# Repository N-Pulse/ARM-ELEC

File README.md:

# N-Pulse Prosthetic Safety System

> **EPFL N-Pulse — Spring Semester 2026**  
> Firmware and GUI for the safety monitoring board of the N-Pulse transradial bionic arm prosthesis.  
> For background on sensor selection rationale, thresholds, and design decisions, refer to the accompanying report.

---

## Repository Structure

```
/
├── GUI/
│   └── serial_dashboard.py        # Plotly Dash web dashboard — reads serial CSV and plots live telemetry
│
└── prosthetic_safety/
    ├── prosthetic_safety.ino      # Arduino sketch entry point (setup + loop)
    ├── Config.h                   # ⬅ All pin assignments, I2C addresses, thresholds — edit here first
    ├── DataTypes.h / .cpp         # Structs (TH_Reading, PowerReading, IMUReading, SafetyFlags) and global sensor objects
    ├── Setup.h / .cpp             # Sensor initialisation and interrupt attachment
    ├── Sensors.h / .cpp           # Sensor read functions (non-blocking DS18B20, SHT41, Si7021, INA260, LIS3DH)
    ├── Safety.h / .cpp            # Fault evaluation logic + ISR handlers
    ├── Logging.h / .cpp           # CSV serial output and SD card stub
    └── Utils.h / .cpp             # Helpers: ROM printing, threshold lookups, raw IMU register I/O
```

---

## Hardware Connections

The system uses two I2C buses on the Adafruit Metro ESP32-S3. Bus 0 (`Wire`, default pins) and Bus 1 (`Wire1`, pins 9 SDA / 10 SCL) are both active simultaneously.

### Pin Map (from `Config.h`)

| Signal | ESP32-S3 Pin | Connected to |
|--------|-------------|--------------|
| SDA0 | Pin SDA | DS2484 bus0, INA260, LIS3DH, SHT41 bus0 |
| SCL0 | Pin SCL | Same as above |
| SDA1 | Pin 9 | DS2484 bus1, SHT41 bus1, Si7021 |
| SCL1 | Pin 10 | Same as above |
| 1-Wire direct | Pin 7 | Battery, socket, and 1 motor DS18B20 (no bridge chip) |
| IMU interrupt | Pin 5 | LIS3DH INT1 → MCU (active-low, pull-up enabled) |
| Current alert | Pin 6 | INA260 ALERT → MCU (active-low, pull-up enabled, latching) |
| Power cut | Pin 11 | Pololu switch CTRL — pull **LOW** to cut load power |

### Wiring Diagram

#### JST cable labels

#### Current interupt test-bench wiring

Depending on the setup, it may be beneficial to make sure VIN- is the same as the systems GND (e.g. when using a lab alim), then wire like on the image (with the jumper). When trying to use the sensor on the test bench with the battery for example, simple pass the high or low cable of the battery through the VIN+ to VIN-. You might want remove the jumper and potentiometer to avoid any confusion in the wiring (unless the grounding is still useful). 

#### Full test-bench

Refer to this image to wire the test bench correctly.

Also note there are 3D printed motor mounts (orange), which can be used to test the motor under load and the thermal sensors. 

#### System-level block diagram and hand-level schematic: 

### I2C Address Map

| Device | Bus | Address | Notes |
|--------|-----|---------|-------|
| DS2484 (×2) | 0 and 1 | `0x18` | Fixed — one per bus to avoid collision |
| LIS3DH | 0 | `0x19` | SDO tied HIGH |
| INA260 | 0 | `0x40` | A0/A1 default |
| SHT41 (×2) | 0 and 1 | `0x44` | Fixed — one per bus to avoid collision |
| Si7021 | 1 | `0x40` | Shares bus 1 with SHT41, different from INA260 on bus 0 |

### DS18B20 Temperature Sensor Topology

Nine DS18B20s are distributed across three 1-Wire lines:

- **Bus 0 (via DS2484 on I2C bus 0):** 3 motor sensors in the hand
- **Bus 1 (via DS2484 on I2C bus 1):** 3 motor sensors in the hand
- **Direct line (pin 7, no bridge):** battery sensor, socket/stump contact sensor, 1 motor sensor

Each DS18B20 line needs a **4.7 kΩ pull-up resistor between DQ and 3.3 V** (but the ones passed in I2C already have a sufficient pullup resistance through the DS2484). The direct line uses the `DallasTemperature` library at **9-bit resolution** (94 ms conversion time, 0.5 °C) for faster updates. The DS2484-bridged lines use the `Adafruit_DS248x` library and the same 94 ms window.

### Power Cut Circuit

```
Battery (+) ──► Power Switch VIN ──► Prosthetic rail (+)
Battery (−) ──► Power Switch GND            ──► Prosthetic rail (−)
                        │
               ESP32-S3 Pin 11 ──► CTRL (LOW = power cut)
```

`PIN_POWER_CUT` is driven LOW by either the main loop (`requestPowerCut()`) or directly from the ISR for minimum latency on overcurrent and shock events.

---

## Sensor Discovery & Address Registration

**When new DS18B20 sensors are installed, their ROM addresses must be registered in `Config.h`.** (This should be already correct if the test-bench wasn't changed.) The firmware will print every discovered ROM to the serial monitor at startup — run the sketch once, note the ROM codes, then fill in the `bus0_sensors[]`, `bus1_sensors[]`, and `direct_sensors[]` arrays with the appropriate `SensorPurpose` and per-sensor temperature limit.

```cpp
// Example entry in Config.h
static constexpr SensorMapping direct_sensors[] = {
  {{ 0x28, 0xFF, 0x64, 0x0E, 0x6D, 0x54, 0x36, 0xC9 }, SensorPurpose::BATTERY, 45.0f },
  {{ 0x28, 0xFF, 0x64, 0x0E, 0x6D, 0x86, 0x2C, 0xE3 }, SensorPurpose::SOCKET,  41.0f },
  ...
};
```

Per-sensor limits (battery: 45 °C, socket contact: 41 °C, motors: 85 °C) are looked up at runtime by ROM address in `getSensorTempLimit()` (`Utils.cpp`). If a sensor's ROM is not in the table, it falls back to `MAX_TEMP_C`.

---

## INA260 Current Sensor — Bench Test

The INA260 sits in **series** with the battery. Before installing in the arm, validate it on a bench:

### Wiring for the test

```
Bench PSU (+) ──► INA260 IN+ ──► INA260 IN− ──► Load ──► Bench PSU (−)
                     │
              I2C to ESP32-S3 (bus 0, address 0x40)
              ALERT pin → ESP32-S3 pin 6
```

> ⚠️ The INA260 has **no galvanic isolation** between the battery ground and the board ground. Make sure both share the same ground reference, or use an isolated bench PSU. (That is the case on the test-bench)

### Recommended bench settings

| Parameter | Value |
|-----------|-------|
| PSU voltage | **12 V** |
| PSU current limit | **100 mA** |

The alert pin is configured in hardware for **overcurrent** (fires when current exceeds `Config::MAX_CURRENT_MA`). During bench testing, `MAX_CURRENT_MA` is set to 40 mA so the alert fires well within the PSU limit — set it back to 5300 mA (or appropriate value) for normal prosthetic operation.

---

## Arduino Libraries Required

Install all of the following via the Arduino Library Manager before compiling:

| Library | Used for |
|---------|---------|
| `Adafruit_INA260` | Current/voltage sensor |
| `Adafruit_LIS3DH` + `Adafruit_Sensor` | IMU |
| `Adafruit_Si7021` | Humidity/temp sensor (socket) |
| `7semi_SHT4x` | Humidity/temp sensors (hand/wrist) |
| `Adafruit_DS248x` | I2C-to-1-Wire bridge (DS2484) |
| `DallasTemperature` | Direct 1-Wire DS18B20 (no bridge) |
| `OneWire` | Required by DallasTemperature |

**Board:** Adafruit Metro ESP32-S3 (install via Arduino Boards Manager → search "esp32" by Espressif).

---

## Uploading the Firmware

1. Open `prosthetic_safety/prosthetic_safety.ino` in Arduino IDE.
2. Select **Board → Adafruit Metro ESP32-S3** and the correct COM/tty port.
3. Upload. On first boot, watch the serial monitor at **115 200 baud** — setup messages are prefixed with `[SETUP]`. Any sensor not found will print a warning; the ROM addresses of all discovered DS18B20s are printed here for registration.

---

## GUI — Live Telemetry Dashboard

`GUI/serial_dashboard.py` is a Plotly Dash web app. It reads the CSV stream from the serial port and displays five real-time subplots plus status LEDs for each safety flag.

### Install dependencies

```bash
pip install pyserial dash plotly pandas
```

### Configure the port

Edit the top of `serial_dashboard.py`:

```python
SERIAL_PORT   = '/dev/cu.usbmodem101'   
BAUD_RATE     = 115200
```
Replace with the correct port address. 

### Run

```bash
python GUI/serial_dashboard.py
```

Then open **http://127.0.0.1:8050** in any browser. The dashboard auto-reconnects if the serial connection drops.

### What is displayed

| Panel | Channels |
|-------|---------|
| Motor Temperatures | bus0_ds1–3, bus1_ds1–3, direct_ds1, socket contact, battery |
| Body Temperatures | Hand, wrist, socket ambient (SHT41 + Si7021) |
| Relative Humidity | Hand, wrist, socket (SHT41 + Si7021) |
| IMU Data | ax, ay, az [g] + vector magnitude |
| Power Data | Current [mA], voltage [V], power [mW] |
| Status LEDs | Temp limit, humidity limit, overcurrent, shock, power cut, sensors OK |

At startup the dashboard performs a one-time health check: any channel that reads `nan`, 0.0 (humidity), or below −10 °C (temperature) is automatically deselected. You can re-enable channels manually using the checklist below the plots.

### CSV format

The firmware emits one comma-separated line every 500 ms (configurable via `Config::LOG_PERIOD_MS`). Lines starting with `#` are ignored by the dashboard. The exact column order is:

```
t_ms, hand_temp_c, hand_rh, wrist_temp_c, wrist_rh, socket_temp_c, socket_rh,
bus0_ds1_c, bus0_ds2_c, bus0_ds3_c, bus1_ds1_c, bus1_ds2_c, bus1_ds3_c,
battery, socket, direct_ds1_c,
imu_ax_g, imu_ay_g, imu_az_g, imu_mag_g,
current_ma, bus_mv, power_mw,
temp_limit_flag, humidity_limit_flag, overcurrent_limit_flag,
shock_flag, power_cut_flag, sensors_ok
```

The code defaults with `PRINT_CSV_HEADER_AT_BOOT = false`. To have the CSV header printed at startup for easier CSV reading, simply set that to `true`.

---

## Enabling Power Cut Actions

All four power-cut triggers are **disabled by default** in `Config.h` for safe development:

```cpp
static const bool ENABLE_POWER_CUT_ON_OVERCURRENT        = false;
static const bool ENABLE_POWER_CUT_ON_OVERHEAT           = false;
static const bool ENABLE_POWER_CUT_ON_OVERHUMIDITY       = false;
static const bool ENABLE_POWER_CUT_ON_CONFIRMED_SHOCK    = false;
```

Set the relevant flag(s) to `true` once you have validated each sensor path end-to-end. The overcurrent and shock paths trigger from the ISR (minimum latency); overheat and humidity are evaluated in the main loop every `LOG_PERIOD_MS`.

Once a power cut is triggered, it **latches** — the flag does not reset automatically. A manual reset (power cycle or serial command) is required before the safety system will re-arm.

## Troubleshooting

If one of the lines is not being detected, it often happens that the pins are not well plugged in on the MCU (the pins tend to slip out).

## What to Add Next

- **SD card logging** — `logToSDCard()` in `Logging.cpp` is empty. The Metro ESP32-S3 has a built-in MicroSD slot and it would be a useful feature for the safety system. 
- **Using MCU Wireless capabilities** — The ESP32-S3 supports WiFi and Bluetooth; useful for reading data without cable connection with the arm.
- **CAN / UART protocol** — Define how fault codes are forwarded to the main prosthetic control board.
- **Prediction capabilities** - The MCU was chosen with a little extra horse power to be able to handle more demanding computations. One idea was to compute gradients and estiimate if one of the metrics was going to exceed the threshold and add a warning. 

## Other

There are two Adafruit DS2484 1Wire to I2C breakout boards left in the box with the test bench.

## Contributors

| Name | Role | Semester |
|------|------|----------|
| Mathis Finckh | Safety System Design & Implementation | Spring 2026 |

*Please update this table when you pick up the project.*

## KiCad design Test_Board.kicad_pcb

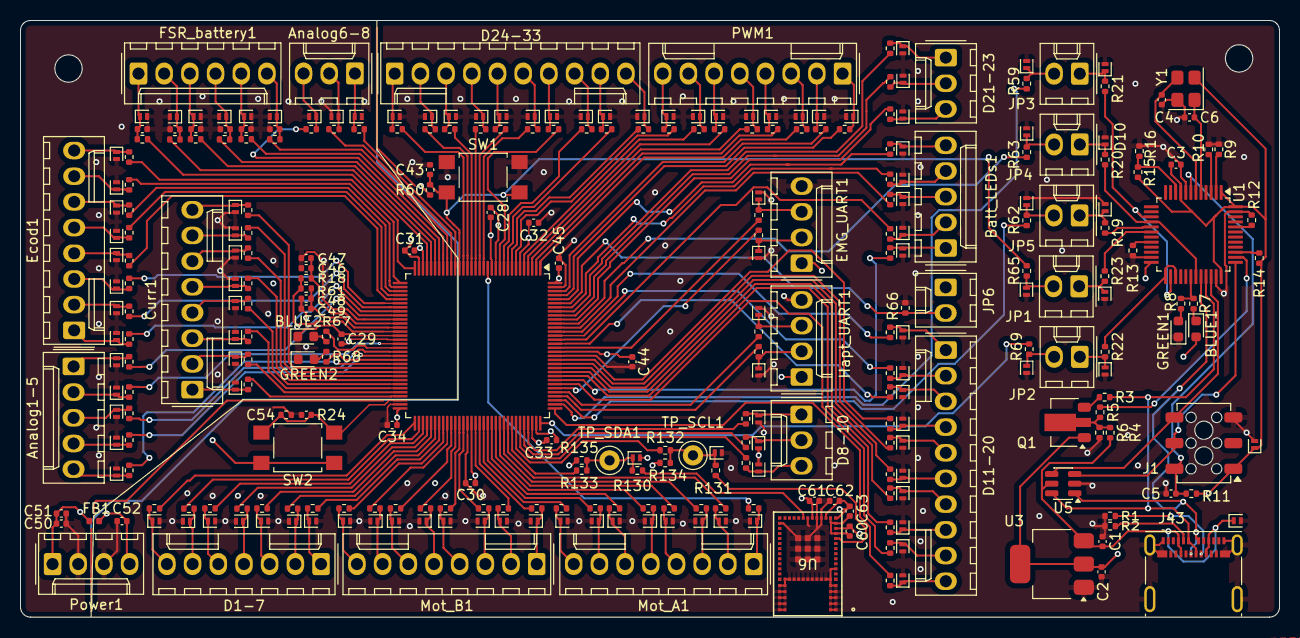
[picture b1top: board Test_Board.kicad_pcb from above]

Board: 4 copper layers, 124.5 x 59.0 mm, 320 parts (0 on the bottom side), 251 nets.

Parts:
Analog1-5: Conn_01x05; Molex_KK-254_AE-6410-05A_1x05_P2.54mm_Vertical
Analog6-8: Conn_01x03; Molex_KK-254_AE-6410-03A_1x03_P2.54mm_Vertical
BLUE1, BLUE2: LED; LED_0603_1608Metric
Batt_LEDs1: Conn_01x05; Molex_KK-254_AE-6410-05A_1x05_P2.54mm_Vertical
C1, C3: 10uF; C_0402_1005Metric
C2, C5, C28, C29, C30, C31, C32, C33, C34, C43, C44, C45, C47, C49, C54, C60, C61, C62, C63: 100nF; C_0402_1005Metric
C4, C6: 15pF; C_0402_1005Metric
C13, C14, C15, C16, C17, C27: 1u; C_0402_1005Metric
C46, C48, C51, C52: 1uF; C_0402_1005Metric
C50: 10nF; C_0402_1005Metric
Curr1: Conn_01x08; Molex_KK-254_AE-6410-08A_1x08_P2.54mm_Vertical
D1, D2, D3, D4, D5, D6, D7, D8, D9, D10, D11, D12, D13, D14, D15, D16, D17, D18, D19, D20, D21, D22, D23, D24, D25, D26, D27, D28, D29, D30, D31, D32, D33, D34, D35, D36, D37, D38, D39, D40, D41, D42, D43, D44, D45, D46, D47, D48, D50, D51, D52, D54, D55, D56, D57, D58, D59, D60, D61, D62, D63, D64, D65, D66, D67, D68, D69, D70, D71, D72, D73, D74, D75, D76, D77, D78, D79, D80, D81, D82, D83, D84, D85, D86, D87, D88, D89, D90, D91, D92, D93, D94, D95, D96, D97, D98, D99, D100, D101, D102, D103, D104, D105, D106, D107, D108, D109, D110, D111, D112: PESD5V0L1UL; D_SOD-882
D1-7: Conn_01x07; Molex_KK-254_AE-6410-07A_1x07_P2.54mm_Vertical
D8-10, D21-23: Conn_01x03; Molex_KK-254_AE-6410-03A_1x03_P2.54mm_Vertical
D11-20, D24-33: Conn_01x10_Pin; Molex_KK-254_AE-6410-10A_1x10_P2.54mm_Vertical
EMG_UART1: Conn_01x04_Pin; Molex_KK-254_AE-6410-04A_1x04_P2.54mm_Vertical
Ecod1: Conn_01x08; Molex_KK-254_AE-6410-08A_1x08_P2.54mm_Vertical
FB1: 120R; L_0402_1005Metric
FSR_battery1: Conn_01x06; Molex_KK-254_AE-6410-06A_1x06_P2.54mm_Vertical
GREEN1, GREEN2: LED; LED_0603_1608Metric
Hapt_UART1: Conn_01x04_Pin; Molex_KK-254_AE-6410-04A_1x04_P2.54mm_Vertical
J1: Conn_02x03_Counter_Clockwise; Harwin_M20-7810345_2x03_P2.54mm_Vertical
J43: USB_C_Receptacle; USB_C_Receptacle_Molex_105450-0101
JP1, JP2, JP3, JP4, JP5: Jumper_2_Bridged; Molex_KK-254_AE-6410-02A_1x02_P2.54mm_Vertical
JP6: Jumper_2_Open; Molex_KK-254_AE-6410-02A_1x02_P2.54mm_Vertical
Mot_A1: Conn_01x08; Molex_KK-254_AE-6410-08A_1x08_P2.54mm_Vertical
Mot_B1: Conn_01x08; Molex_KK-254_AE-6410-08A_1x08_P2.54mm_Vertical
PWM1: Conn_01x08; Molex_KK-254_AE-6410-08A_1x08_P2.54mm_Vertical
Power1: Conn_01x04_Pin; Molex_KK-254_AE-6410-04A_1x04_P2.54mm_Vertical
Q1: NPN; SOT-89-3
R1, R2, R14, R15, R16: 4.7k; R_0402_1005Metric
R3: 1.5k; R_0402_1005Metric
R4, R9, R10, R12, R13, R66: 10k; R_0402_1005Metric
R5, R7, R8, R67, R68: 100; R_0402_1005Metric
R6: 33k; R_0402_1005Metric
R11, R24, R60: 100k; R_0402_1005Metric
R17, R19, R20, R21, R22, R23, R25, R26, R27, R28, R34, R35, R36, R37, R38, R39, R40, R41, R42, R44, R45, R46, R47, R48, R49, R50, R51, R52, R53, R54, R55, R56, R57, R58, R59, R62, R63, R64, R65, R69, R70, R71, R72, R73, R74, R75, R76, R77, R78, R79, R80, R81, R82, R83, R84, R85, R86, R87, R88, R89, R90, R91, R92, R93, R94, R95, R96, R97, R98, R99, R100, R101, R102, R103, R104, R105, R106, R107, R108, R109, R110, R111, R112, R113, R114, R115, R116, R117, R118, R119, R120, R121, R122, R123, R124, R125, R126, R127, R128, R129, R130, R131, R132, R133: 47; R_0402_1005Metric
R18, R29, R30, R31, R32, R33, R43, R61: 1k; R_0402_1005Metric
R134, R135: 2k2; R_0402_1005Metric
SW1, SW2: SW_Push; SW_SPST_TL3305B
TP_SCL1: TestPoint; TestPoint_Keystone_5000-5004_Miniature
TP_SDA1: TestPoint; TestPoint_Keystone_5000-5004_Miniature
U1: STM32F103CBTx; LQFP-48_7x7mm_P0.5mm
U2: STM32G474QETx; LQFP-128_14x14mm_P0.4mm
U3: LD1117S33TR_SOT223; SOT-223-3_TabPin2
U5: SRV05-4; SOT-23-6
U6: STM32WB1MMCH6TR; LGA77_6P5X10_STM
Y1: 8MHz; Crystal_SMD_3225-4Pin_3.2x2.5mm

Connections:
+3.3VA: C50.1, C51.1, FB1.1, Power1.1, R18.1, R61.2, U2.45 (VDDA)
+3V3: BLUE1.2 (A), C2.1, C3.1, C28.1, C29.1, C30.1, C31.1, C32.1, C33.1, C34.1, C44.1, C45.1, C52.1, C60.1, C61.1, C62.1, C63.1, D4.1 (K), EMG_UART1.1, FB1.2, Hapt_UART1.1, J1.1, JP6.1 (A), Power1.4, Q1.1 (C), R11.2, R14.1, R15.2, R60.2, R134.1, R135.1, SW2.1, U1.1 (VBAT), U1.9 (VDDA), U1.24 (VDD), U1.36 (VDD), U1.48 (VDD), U2.6 (VBAT), U2.13 (VDD), U2.31 (VDD), U2.47 (VDD), U2.64 (VDD), U2.79 (VDD), U2.95 (VDD), U2.111 (VDD), U2.128 (VDD), U3.2 (VO), U6.16 (VDDA), U6.18 (VBAT), U6.20 (VDDSMPS), U6.23 (NRST), Y1.2
/Blth_I2C_SCL: D2.1 (K), R131.2, R132.2, R134.2, TP_SCL1.1
/Blth_I2C_SDA: D1.1 (K), R130.2, R133.2, R135.2, TP_SDA1.1
/Custom-debugger/D+: J43.A6 (D+), J43.B6 (D+), R3.2, U1.33 (PA12), U5.6 (IO4)
/Custom-debugger/D-: J43.A7 (D-), J43.B7 (D-), U1.32 (PA11), U5.1 (IO1)
/Custom-debugger/JTDI: D7.1 (K), JP5.1 (A), R19.2
/Custom-debugger/NRST: D9.1 (K), JP1.1 (A), R23.2
/Custom-debugger/NRST_IN: C5.1, J1.4, R11.1, U1.7 (NRST)
/Custom-debugger/SWCLK_IN: J1.5, U1.37 (PA14), U5.3 (IO2)
/Custom-debugger/SWCLK/JTCLK: D11.1 (K), JP3.1 (A), R21.2
/Custom-debugger/SWDIO_IN: J1.6, U1.34 (PA13), U5.4 (IO3)
/Custom-debugger/SWDIO/JTMS: D8.1 (K), JP2.1 (A), R22.2
/Custom-debugger/SWO/JTDO: D10.1 (K), JP4.1 (A), R20.2
/JTDI: R62.2, U2.99 (PA15)
/NRST: C43.1, R60.1, R65.2, SW1.1, U2.21 (PG10)
/SWCLK: R59.2, U2.98 (PA14)
/SWDIO: R69.2, U2.96 (PA13)
/SWO: R63.2, U2.118 (PB3)
Anlg_1: R34.2, U2.53 (PE7)
Anlg_2: R36.2, U2.51 (PF14)
Anlg_3: R37.2, U2.50 (PF13)
Anlg_4: R38.2, U2.48 (PF11)
Anlg_5: R39.2, U2.41 (PB2)
Anlg_6: R40.2, U2.26 (PF2)
Anlg_7: R41.2, U2.23 (PC1)
Anlg_8: R42.2, U2.22 (PC0)
BOOT_0: JP6.2 (B), R66.2, U2.123 (PB8)
Batt_LED_1: R126.2, U2.104 (PG6)
Batt_LED_2: R127.2, U2.114 (PD4)
Batt_LED_3: R128.2, U2.117 (PD7)
Batt_LED_4: R125.2, U2.122 (PB7)
Batt_LED_5: R124.2, U2.124 (PB9)
Battery_lvl: R43.2, U2.32 (PA3)
Button: C54.1, R24.1, SW2.2, U2.62 (PB10)
Curr1: R17.2, U2.61 (PE15)
Curr2: R129.2, U2.60 (PE14)
Curr3: R25.2, U2.59 (PE13)
Curr4: R26.2, U2.58 (PE12)
Curr5: R27.2, U2.57 (PE11)
Curr6: R28.2, U2.56 (PE10)
Curr7: R35.2, U2.55 (PE9)
Curr8: R64.2, U2.54 (PE8)
EMG_UART_RX: R71.2, U2.112 (PD2)
EMG_UART_TX: R70.2, U2.102 (PC12)
Ecod_1: R51.2, U2.40 (PB1)
Ecod_2: R52.2, U2.39 (PB0)
Ecod_3: R53.2, U2.38 (PC5)
Ecod_4: R54.2, U2.37 (PC4)
Ecod_5: R55.2, U2.36 (PA7)
Ecod_6: R56.2, U2.35 (PA6)
Ecod_7: R57.2, U2.34 (PA5)
Ecod_8: R58.2, U2.33 (PA4)
FSR1: R29.2, U2.24 (PC2)
FSR2: R30.2, U2.25 (PC3)
FSR3: R31.2, U2.27 (PA0)
FSR4: R32.2, U2.28 (PA1)
FSR5: R33.2, U2.29 (PA2)
GND: BLUE2.1 (K), C1.2, C2.2, C3.2, C4.2, C5.2, C6.2, C13.2, C14.2, C15.2, C16.2, C17.2, C27.2, C28.2, C29.2, C30.2, C31.2, C32.2, C33.2, C34.2, C43.2, C44.2, C45.2, C46.2, C47.2, C48.1, C49.1, C50.2, C51.2, C52.2, C54.2, C60.2, C61.2, C62.2, C63.2, D1.2 (A), D2.2 (A), D3.2 (A), D4.2 (A), D5.2 (A), D6.2 (A), D7.2 (A), D8.2 (A), D9.2 (A), D10.2 (A), D11.2 (A), D12.2 (A), D13.2 (A), D14.2 (A), D15.2 (A), D16.2 (A), D17.2 (A), D18.2 (A), D19.2 (A), D20.2 (A), D21.2 (A), D22.2 (A), D23.2 (A), D24.2 (A), D25.2 (A), D26.2 (A), D27.2 (A), D28.2 (A), D29.2 (A), D30.2 (A), D31.2 (A), D32.2 (A), D33.2 (A), D34.2 (A), D35.2 (A), D36.2 (A), D37.2 (A), D38.2 (A), D39.2 (A), D40.2 (A), D41.2 (A), D42.2 (A), D43.2 (A), D44.2 (A), D45.2 (A), D46.2 (A), D47.2 (A), D48.2 (A), D50.2 (A), D51.2 (A), D52.2 (A), D54.2 (A), D55.2 (A), D56.2 (A), D57.2 (A), D58.2 (A), D59.2 (A), D60.2 (A), D61.2 (A), D62.2 (A), D63.2 (A), D64.2 (A), D65.2 (A), D66.2 (A), D67.2 (A), D68.2 (A), D69.2 (A), D70.2 (A), D71.2 (A), D72.2 (A), D73.2 (A), D74.2 (A), D75.2 (A), D76.2 (A), D77.2 (A), D78.2 (A), D79.2 (A), D80.2 (A), D81.2 (A), D82.2 (A), D83.2 (A), D84.2 (A), D85.2 (A), D86.2 (A), D87.2 (A), D88.2 (A), D89.2 (A), D90.2 (A), D91.2 (A), D92.2 (A), D93.2 (A), D94.2 (A), D95.2 (A), D96.2 (A), D97.2 (A), D98.2 (A), D99.2 (A), D100.2 (A), D101.2 (A), D102.2 (A), D103.2 (A), D104.2 (A), D105.2 (A), D106.2 (A), D107.2 (A), D108.2 (A), D109.2 (A), D110.2 (A), D111.2 (A), D112.2 (A), EMG_UART1.4, GREEN1.1 (K), GREEN2.1 (K), Hapt_UART1.4, J1.3, J43.A1 (GND), J43.A12 (GND), J43.B1 (GND), J43.B12 (GND), J43.S1 (SHIELD), Power1.2, Power1.3, R1.2, R2.2, R6.2, R9.1, R10.1, R12.1, R13.1, R16.1, R24.2, R66.1, SW1.2, U1.8 (VSSA), U1.23 (VSS), U1.35 (VSS), U1.47 (VSS), U2.12 (VSS), U2.30 (VSS), U2.42 (VSSA), U2.46 (VSS), U2.63 (VSS), U2.78 (VSS), U2.94 (VSS), U2.110 (VSS), U2.127 (VSS), U3.1 (GND), U5.2 (VN), U6.1 (VSS), U6.2 (VSS), U6.3 (VSS), U6.4 (VSS), U6.5 (VSSRF), U6.8 (VSSRF), U6.15 (VSS), U6.17 (VSS), U6.19 (VSS), U6.21 (VSSSMPS), U6.22 (BOOT0), U6.24 (VSS), U6.31 (VSS), U6.43 (VSS), U6.44 (VSS), U6.45 (VSS), U6.46 (VSS), U6.47 (VSS), U6.48 (VSS), U6.49 (VSS), U6.50 (VSS), U6.51 (VSS), U6.52 (VSS), U6.53 (VSS), U6.54 (VSS), U6.55 (VSS), U6.56 (VSS), U6.57 (VSS), U6.58 (VSS), U6.59 (VSS), U6.60 (VSS), U6.61 (VSS), U6.62 (VSS), U6.63 (VSS), U6.64 (VSS), U6.65 (VSS), U6.66 (VSS), U6.67 (VSS), U6.68 (VSS), U6.69 (VSS), U6.70 (VSS), U6.71 (VSS), U6.72 (VSS), U6.73 (VSS), U6.74 (VSS), U6.75 (VSS), U6.76 (VSS), U6.77 (VSS), Y1.4
GPIO_1: R91.2, U2.65 (PB11)
GPIO_2: R92.2, U2.66 (PB12)
GPIO_3: R93.2, U2.67 (PB13)
GPIO_4: R94.2, U2.68 (PB14)
GPIO_5: R95.2, U2.69 (PB15)
GPIO_6: R96.2, U2.70 (PD8)
GPIO_7: R97.2, U2.71 (PD9)
GPIO_8: R98.2, U2.91 (PA10)
GPIO_9: R99.2, U2.92 (PA11)
GPIO_10: R100.2, U2.93 (PA12)
GPIO_11: R101.2, U2.97 (PF6)
GPIO_12: R102.2, U2.103 (PG5)
GPIO_13: R103.2, U2.105 (PG7)
GPIO_14: R104.2, U2.106 (PG8)
GPIO_15: R105.2, U2.107 (PG9)
GPIO_16: R110.2, U2.108 (PD0)
GPIO_17: R109.2, U2.109 (PD1)
GPIO_18: R108.2, U2.113 (PD3)
GPIO_19: R107.2, U2.115 (PD5)
GPIO_20: R106.2, U2.116 (PD6)
GPIO_21: R111.2, U2.119 (PB4)
GPIO_22: R112.2, U2.120 (PB5)
GPIO_23: R113.2, U2.121 (PB6)
GPIO_24: R114.2, U2.8 (PC14)
GPIO_25: R115.2, U2.9 (PC15)
GPIO_26: R116.2, U2.10 (PF3)
GPIO_27: R117.2, U2.11 (PF4)
GPIO_28: R118.2, U2.15 (PF7)
GPIO_29: R123.2, U2.16 (PF8)
GPIO_30: R122.2, U2.17 (PF9)
GPIO_31: R121.2, U2.18 (PF10)
GPIO_32: R120.2, U2.19 (PF0)
GPIO_33: R119.2, U2.20 (PF1)
Hapt_UART_RX: R73.2, U2.101 (PC11)
Hapt_UART_TX: R72.2, U2.100 (PC10)
LED1: R67.1, U2.49 (PF12)
LED2: R68.1, U2.52 (PF15)
Mot1_A: R74.2, U2.14 (PF5)
Mot1_B: R82.2, U2.81 (PC7)
Mot2_A: R75.2, U2.88 (PC9)
Mot2_B: R83.2, U2.80 (PC6)
Mot3_A: R76.2, U2.87 (PC8)
Mot3_B: R84.2, U2.77 (PD15)
Mot4_A: R77.2, U2.86 (PG4)
Mot4_B: R85.2, U2.76 (PD14)
Mot5_A: R78.2, U2.85 (PG3)
Mot5_B: R86.2, U2.75 (PD13)
Mot6_A: R79.2, U2.84 (PG2)
Mot6_B: R87.2, U2.74 (PD12)
Mot7_A: R80.2, U2.83 (PG1)
Mot7_B: R88.2, U2.73 (PD11)
Mot8_A: R81.2, U2.82 (PG0)
Mot8_B: R89.2, U2.72 (PD10)
unnamed: Analog1-5.1, D27.1 (K), R39.1
unnamed: Analog1-5.2, D26.1 (K), R38.1
unnamed: Analog1-5.3, D25.1 (K), R37.1
unnamed: Analog1-5.4, D24.1 (K), R36.1
unnamed: Analog1-5.5, D23.1 (K), R34.1
unnamed: Analog6-8.1, D30.1 (K), R42.1
unnamed: Analog6-8.2, D29.1 (K), R41.1
unnamed: Analog6-8.3, D28.1 (K), R40.1
unnamed: BLUE1.1 (K), R7.2
unnamed: BLUE2.2 (A), R67.2
unnamed: Batt_LEDs1.1, D80.1 (K), R126.1
unnamed: Batt_LEDs1.2, D96.1 (K), R127.1
unnamed: Batt_LEDs1.3, D101.1 (K), R128.1
unnamed: Batt_LEDs1.4, D109.1 (K), R125.1
unnamed: Batt_LEDs1.5, D110.1 (K), R124.1
unnamed: Curr1.1, D5.1 (K), R17.1
unnamed: Curr1.2, D6.1 (K), R129.1
unnamed: Curr1.3, D12.1 (K), R25.1
unnamed: Curr1.4, D13.1 (K), R26.1
unnamed: Curr1.5, D14.1 (K), R27.1
unnamed: Curr1.6, D15.1 (K), R28.1
unnamed: Curr1.7, D16.1 (K), R35.1
unnamed: Curr1.8, D22.1 (K), R64.1
unnamed: D1-7.1, D81.1 (K), R97.1
unnamed: D1-7.2, D79.1 (K), R96.1
unnamed: D1-7.3, D78.1 (K), R95.1
unnamed: D1-7.4, D77.1 (K), R94.1
unnamed: D1-7.5, D76.1 (K), R93.1
unnamed: D1-7.6, D75.1 (K), R92.1
unnamed: D1-7.7, D74.1 (K), R91.1
unnamed: D8-10.1, D85.1 (K), R100.1
unnamed: D8-10.2, D84.1 (K), R99.1
unnamed: D8-10.3, D82.1 (K), R98.1
unnamed: D11-20.1, D90.1 (K), R106.1
unnamed: D11-20.2, D91.1 (K), R107.1
unnamed: D11-20.3, D92.1 (K), R108.1
unnamed: D11-20.4, D93.1 (K), R109.1
unnamed: D11-20.5, D94.1 (K), R110.1
unnamed: D11-20.6, D89.1 (K), R105.1
unnamed: D11-20.7, D88.1 (K), R104.1
unnamed: D11-20.8, D87.1 (K), R103.1
unnamed: D11-20.9, D86.1 (K), R102.1
unnamed: D11-20.10, D83.1 (K), R101.1
unnamed: C13.1, D17.1 (K), FSR_battery1.6, R29.1
unnamed: C14.1, D18.1 (K), FSR_battery1.5, R30.1
unnamed: C15.1, D19.1 (K), FSR_battery1.4, R31.1
unnamed: C16.1, D20.1 (K), FSR_battery1.3, R32.1
unnamed: D21-23.1, D99.1 (K), R113.1
unnamed: D21-23.2, D98.1 (K), R112.1
unnamed: D21-23.3, D97.1 (K), R111.1
unnamed: C17.1, D21.1 (K), FSR_battery1.2, R33.1
unnamed: C27.1, D31.1 (K), FSR_battery1.1, R43.1
unnamed: D32.1 (K), PWM1.1, R44.1
unnamed: D33.1 (K), PWM1.2, R45.1
unnamed: D34.1 (K), PWM1.3, R46.1
unnamed: D35.1 (K), PWM1.4, R47.1
unnamed: D36.1 (K), PWM1.5, R48.1
unnamed: D37.1 (K), PWM1.6, R49.1
unnamed: D38.1 (K), PWM1.7, R50.1
unnamed: D39.1 (K), Ecod1.1, R51.1
unnamed: D40.1 (K), Ecod1.2, R52.1
unnamed: D41.1 (K), Ecod1.3, R53.1
unnamed: D42.1 (K), Ecod1.4, R54.1
unnamed: D43.1 (K), Ecod1.5, R55.1
unnamed: D44.1 (K), Ecod1.6, R56.1
unnamed: D45.1 (K), Ecod1.7, R57.1
unnamed: D46.1 (K), Mot_A1.1, R74.1
unnamed: D47.1 (K), JP4.2 (B), R63.1
unnamed: D48.1 (K), Ecod1.8, R58.1
unnamed: D50.1 (K), JP5.2 (B), R62.1
unnamed: D51.1 (K), JP3.2 (B), R59.1
unnamed: D52.1 (K), JP2.2 (B), R69.1
unnamed: D54.1 (K), EMG_UART1.2, R70.1
unnamed: D55.1 (K), EMG_UART1.3, R71.1
unnamed: D56.1 (K), Hapt_UART1.3, R73.1
unnamed: D57.1 (K), Hapt_UART1.2, R72.1
unnamed: D58.1 (K), Mot_A1.2, R75.1
unnamed: D59.1 (K), Mot_A1.3, R76.1
unnamed: D60.1 (K), Mot_A1.4, R77.1
unnamed: D61.1 (K), Mot_A1.5, R78.1
unnamed: D62.1 (K), Mot_A1.6, R79.1
unnamed: D63.1 (K), Mot_A1.7, R80.1
unnamed: D64.1 (K), Mot_A1.8, R81.1
unnamed: D65.1 (K), Mot_B1.1, R82.1
unnamed: D66.1 (K), Mot_B1.2, R83.1
unnamed: D67.1 (K), Mot_B1.3, R84.1
unnamed: D68.1 (K), Mot_B1.4, R85.1
unnamed: D69.1 (K), Mot_B1.5, R86.1
unnamed: D70.1 (K), Mot_B1.6, R87.1
unnamed: D71.1 (K), Mot_B1.7, R88.1
unnamed: D72.1 (K), Mot_B1.8, R89.1
unnamed: D73.1 (K), PWM1.8, R90.1
unnamed: D95.1 (K), JP1.2 (B), R65.1
unnamed: D24-33.10, D100.1 (K), R114.1
unnamed: D24-33.9, D102.1 (K), R115.1
unnamed: D24-33.8, D103.1 (K), R116.1
unnamed: D24-33.7, D104.1 (K), R117.1
unnamed: D24-33.6, D105.1 (K), R118.1
unnamed: D24-33.1, D106.1 (K), R119.1
unnamed: D24-33.2, D107.1 (K), R120.1
unnamed: D24-33.3, D108.1 (K), R121.1
unnamed: D24-33.4, D111.1 (K), R122.1
unnamed: D24-33.5, D112.1 (K), R123.1
unnamed: GREEN1.2 (A), R8.2
unnamed: GREEN2.2 (A), R68.2
unnamed: J43.A5 (CC1), R2.1
unnamed: J43.B5 (CC2), R1.1
unnamed: Q1.2 (B), R4.2, R5.1, R6.1
unnamed: Q1.3 (E), R3.1
unnamed: R12.2, U1.44 (BOOT0)
unnamed: R15.1, R16.2, U1.10 (PA0)
unnamed: R21.1, U1.15 (PA5), U1.26 (PB13)
unnamed: R19.1, U1.17 (PA7)
unnamed: R7.1, R8.1, U1.30 (PA9)
unnamed: R20.1, U1.16 (PA6), U1.31 (PA10)
unnamed: R5.2, U1.38 (PA15)
unnamed: R23.1, U1.18 (PB0)
unnamed: R13.2, U1.20 (PB2)
unnamed: R14.2, U1.39 (PB3)
unnamed: R22.1, U1.25 (PB12), U1.27 (PB14)
unnamed: R9.2, U1.2 (PC13)
unnamed: R10.2, U1.3 (PC14)
unnamed: C6.1, U1.5 (PD0), Y1.1
unnamed: C4.1, U1.6 (PD1), Y1.3
unnamed: R133.1, U2.89 (PA8)
unnamed: R132.1, U2.90 (PA9)
unnamed: C46.1, C47.1, R18.2, U2.43 (VREF+)
unnamed: C48.2, C49.2, R61.1, U2.44 (VREF_+)
unnamed: R130.1, U6.25 (PB7)
unnamed: R131.1, U6.14 (PB8)
PWM_Mot1: R44.2, U2.125 (PE0)
PWM_Mot2: R45.2, U2.126 (PE1)
PWM_Mot3: R46.2, U2.1 (PE2)
PWM_Mot4: R47.2, U2.2 (PE3)
PWM_Mot5: R48.2, U2.3 (PE4)
PWM_Mot6: R49.2, U2.4 (PE5)
PWM_Mot7: R50.2, U2.5 (PE6)
PWM_Mot8: R90.2, U2.7 (PC13)
VBUS: C1.1, D3.1 (K), J43.A4 (VBUS), J43.A9 (VBUS), J43.B4 (VBUS), J43.B9 (VBUS), R4.1, U3.3 (VI), U5.5 (VP)

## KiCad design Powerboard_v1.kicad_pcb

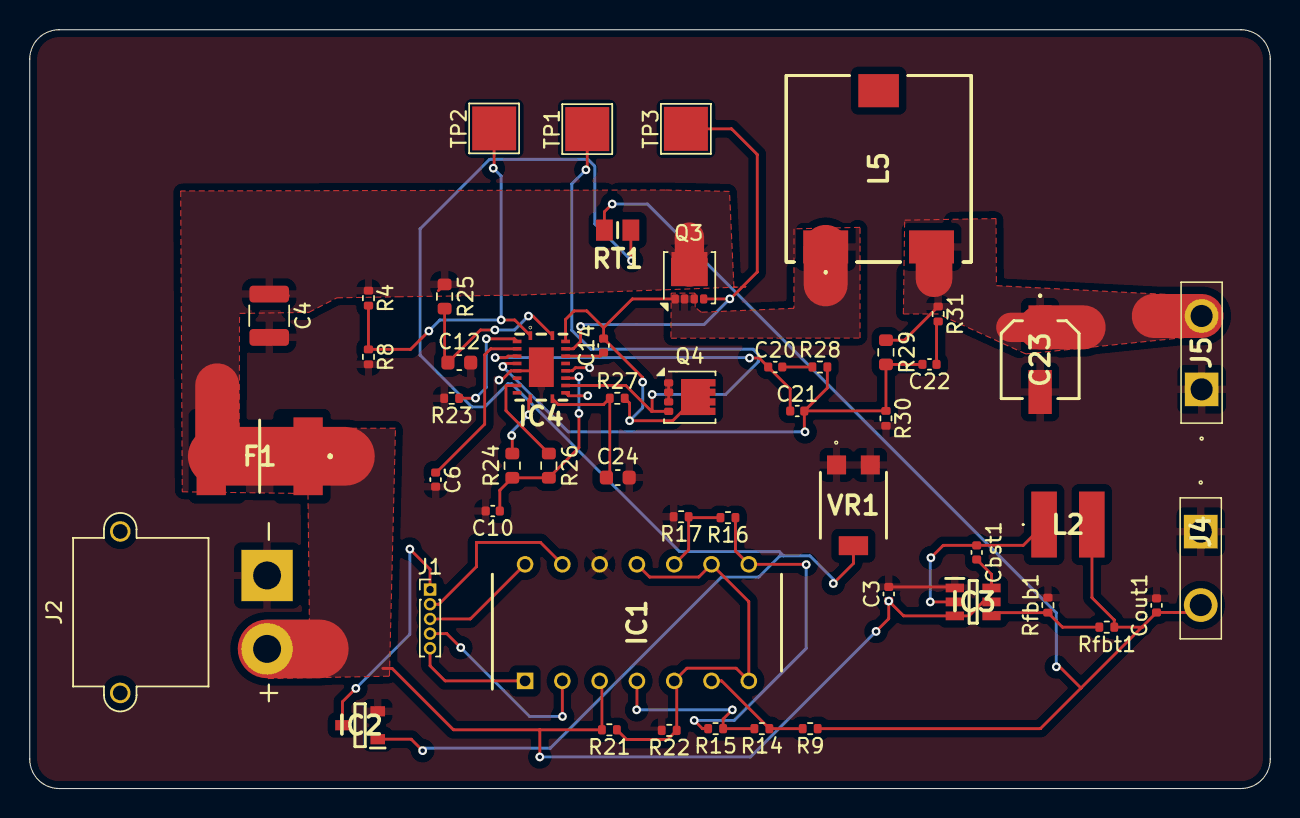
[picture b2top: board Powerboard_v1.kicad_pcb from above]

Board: 2 copper layers, 84.5 x 51.7 mm, 51 parts (0 on the bottom side), 34 nets.

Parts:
C3: 10uF; C_0402_1005Metric
C4: 4.7uF 50V; C_1210_3225Metric
C6: 56nF; C_0402_1005Metric
C10: 2.2uF; C_0402_1005Metric
C12: CGA3E2X7R1H104K080AA; C_0603_1608Metric
C14: GCM1555C1H100FA16D; C_0402_1005Metric
C20: 8200pF; C_0402_1005Metric
C21, C22: 680pF; C_0402_1005Metric
C23: 56uF 20 V; 16SVF82M
C24: 10pF 100Vdc; C_0603_1608Metric
Cbst1: 100nF; C_0402_1005Metric
Cout1: 22uF; C_0402_1005Metric
F1: Fuse; 2920L07560MR
IC1: LM339N; DIP794W53P254L1930H508Q14N
IC2: MMBT3904; SOT95P240X120-3N
IC3: TPS563200DDCR; SOT95P280X110-6N
IC4: LM25145RGYR; RGY0020B
J1: Conn_01x05_Pin; PinHeader_1x05_P1.00mm_Vertical
J2: Conn_01x02_Socket; AMASS_XT30PW-M_1x02_P2.50mm_Horizontal
J4, J5: 1.5 mm; 1933189
L2: SDE0403AT-3R3M; SDE0403AT3R3M
L5: 2.7uH 2.6mOhms; SER1360272KLD
Q3: 35A, 30V; VSON-8_3.3x3.3mm_P0.65mm_NexFET
Q4: 35A Id, 30V Vds; VSON-8_3.3x3.3mm_P0.65mm_NexFET
R4: 69.8k; R_0402_1005Metric
R8: 8.25k; R_0402_1005Metric
R9: 1,1k; R_0402_1005Metric
R14, R15, R16: 300; R_0402_1005Metric
R17: 3k; R_0402_1005Metric
R21: 10kOhm; R_0402_1005Metric
R22: 3,3kOhm; R_0402_1005Metric
R23: 39.2k; R_0402_1005Metric
R24: 20k; R_0603_1608Metric
R25: 2.1ohms 1%; R_0603_1608Metric
R26: 20 kOhms; R_0603_1608Metric
R27: 1.24k; R_0402_1005Metric
R28: 2.37k; R_0402_1005Metric
R29: 18k; R_0603_1608Metric
R30: 1.27K; R_0402_1005Metric
R31: 2.49k; R_0402_1005Metric
RT1: NCP18XH103F0SRB; THRMC2012X130N
Rfbb1: 10kOhm; R_0402_1005Metric
Rfbt1: 56.2kOhm; R_0402_1005Metric
TP1, TP2, TP3: TestPoint; TestPoint_Pad_3.0x3.0mm
VR1: 3314G-1-102E

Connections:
5V circuit: Cout1.1, J4.2, L2.2, R9.1, RT1.1, Rfbt1.1
Batt +: C3.1, C4.1, F1.1, F1.2, IC1.3 (VCC), IC3.3 (VIN), IC3.5 (EN), J2.2, Q3.5 (D), R4.1, R21.2, R25.1
GND: C3.2, C4.2, C6.2, C10.2, C12.2, C23.2 (-), C24.2, Cout1.2, IC1.12 (GND), IC2.2 (E), IC3.1 (GND), IC4.6 (AGND), IC4.12 (PGND), IC4.15 (EP_1), IC4.21 (EP_2), J2.1, J4.1, J5.1, Q4.1 (S), Q4.2 (S), Q4.3 (S), R8.2, R17.2, R22.2, R23.2, R30.2, Rfbb1.2, VR1.1 (CW), VR1.3 (WIPER)
unnamed: C20.2, R28.1
unnamed: C22.1, R31.2
unnamed: C23.1 (+), J5.2, L5.2, R29.1, R31.1
unnamed: IC1.5 (2IN+), IC1.7 (1IN+), IC1.9 (3IN+), IC1.11 (4IN+), R21.1, R22.1
unnamed: IC1.6 (1IN-), R9.2, R14.1
unnamed: IC1.1 (1OUT), J1.5
unnamed: IC1.4 (2IN-), R14.2, R15.1
unnamed: IC1.2 (2OUT), J1.4
unnamed: IC1.8 (3IN-), R15.2, R16.1
unnamed: IC1.10 (4IN-), R16.2, R17.1
unnamed: IC1.14 (OUT3), J1.3
unnamed: IC1.13 (OUT4), J1.2
unnamed: IC2.1 (B), RT1.2, VR1.2 (CCW)
unnamed: Cbst1.1, IC3.2 (SW), L2.1
unnamed: Cbst1.2, IC3.6 (VBST)
unnamed: IC3.4 (VFB), Rfbb1.1, Rfbt1.2
unnamed: C14.1, IC4.17 (BST)
unnamed: C20.1, C21.1, IC4.4 (COMP)
unnamed: IC4.1 (EN/UVLO), R4.2, R8.1, TP2.1
unnamed: C21.2, C22.2, IC4.5 (FB), R28.2, R29.2, R30.1
unnamed: IC4.18 (HO), Q3.4 (G), TP3.1
unnamed: C24.1, IC4.11 (ILIM), R27.1
unnamed: IC4.13 (LO), Q4.4 (G), TP1.1
unnamed: IC4.10 (PGOOD), R24.2
unnamed: IC4.2 (RT), R23.1
unnamed: C6.1, IC4.3 (SS/TRK)
unnamed: C14.2, IC4.19 (SW), L5.1, Q3.1 (S), Q3.2 (S), Q3.3 (S), Q4.5 (D), R27.2
unnamed: IC4.8 (SYNCIN), R26.1
unnamed: C10.1, IC4.14 (VCC), R24.1, R26.2
unnamed: C12.1, IC4.20 (VIN), R25.2
Temp: IC2.3 (C), J1.1

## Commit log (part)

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2025-11-15 Initialize README with project title and description
    Added project title and description to README.
2025-11-17 schematics files for review
    - Test_Board.kicad_sch is the root
    - contact Clément Fully - ARM EL on slack if needed
2025-11-17 MCU test board schematics for review
    Root file is Test_Board
    Contact Clement Fully - ARM EL on slack if needed
2025-11-20 Current Version of schematics to review
2025-11-25 Reviewed schematics
2025-11-25 PCB files to review
2025-12-14 Powerboard schematics done
2025-12-15 Addition of individual sub folders
2025-12-15 corrected version with better connections for high power
2025-12-15 Corrected fuse footprint
2025-12-15 PCB file reviewed
2025-12-15 Schematics reviewed
2025-12-20 board corrrigée
2026-01-09 Complete project file
2026-03-14 PCB and Gerber files final
2026-03-14 Datasheet for MCU test board
2026-04-22 Powerboard v2 ready
2026-04-25 Updated silkscreen on V2
2026-06-16 Replace submodule with actual files
2026-06-16 README update + docs
2026-06-16 added requirements.txt
